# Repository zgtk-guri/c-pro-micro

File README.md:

# c-pro-micro
The atmega32u4 micro-controller board with USB Type-C receptacle, which is compatible with SparkFun Pro Micro

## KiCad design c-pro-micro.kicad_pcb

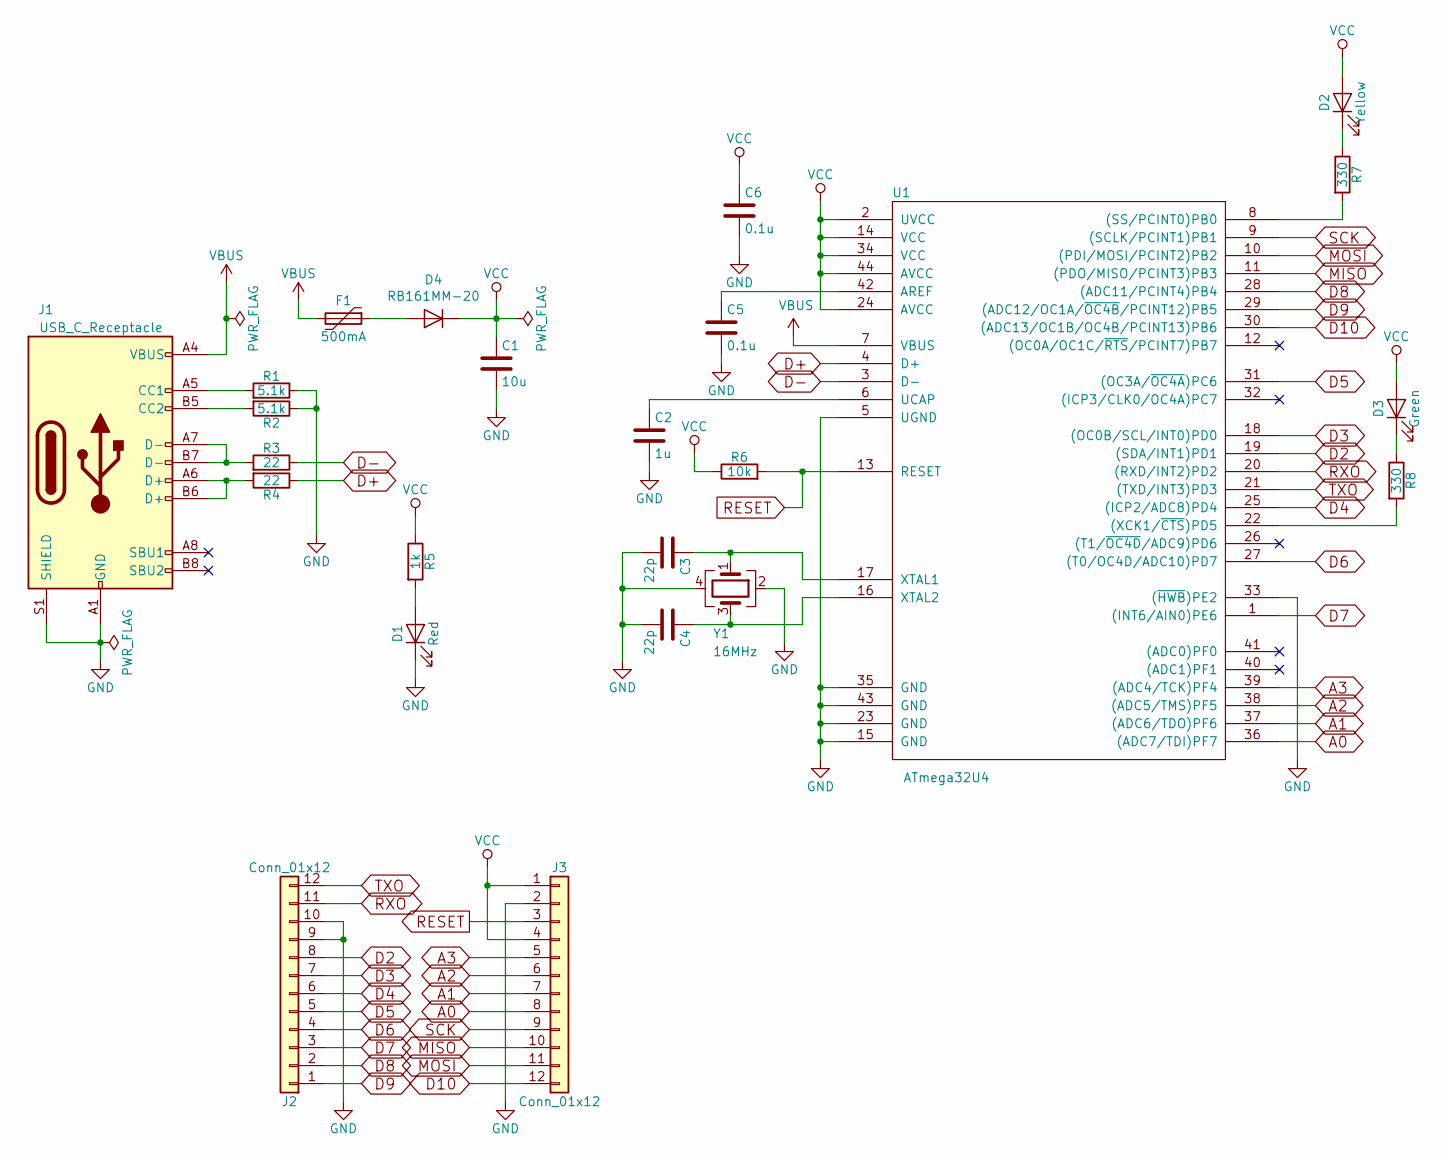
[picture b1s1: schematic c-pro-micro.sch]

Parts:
C1: 10u; C_0603_1608Metric; MPN CL10A106KP8NNNC
C2: 1u; C_0402_1005Metric
C3, C4: 22p; C_0402_1005Metric; MPN 0402CG220J500NT
C5, C6: 0.1u; C_0402_1005Metric; MPN CL05B104KO5NNNC
D1: Red; LED_0603_1608Metric
D2: Yellow; LED_0603_1608Metric
D3: Green; LED_0603_1608Metric
D4: RB161MM-20; D_SOD-123F
F1: 500mA; Fuse_1206_3216Metric
J1: USB_C_Receptacle; CX90M-16P; MPN CX90M-16P; DigikeyPN H126318CT-ND
J2: Conn_01x12; ProMicro_LeftPinhead
J3: Conn_01x12; ProMicro_RightPinhead
R1, R2: 5.1k; R_0402_1005Metric; MPN 0603WAF5101T5E
R3, R4: 22; R_0402_1005Metric; MPN 0402WGF220JTCE
R5: 1k; R_0402_1005Metric; MPN 0402WGF1001TCE
R6: 10k; R_0402_1005Metric; MPN 0402WGF1002TCE
R7, R8: 330; R_0402_1005Metric
U1: ATmega32U4; QFN-44-1EP_7x7mm_Pitch0.5mm_without_bottom; MPN ATMEGA32U4-MUR; DigikeyPN ATMEGA32U4-MURCT-ND
Y1: 16MHz; Crystal_SMD_SeikoEpson_FA238-4Pin_3.2x2.5mm; MPN FA-238 16.0000MB-C3; DigikeyPN SER3686CT-ND

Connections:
A0: J3.8, U1.36 ((ADC7/TDI)PF7)
A1: J3.7, U1.37 ((ADC6/TDO)PF6)
A2: J3.6, U1.38 ((ADC5/TMS)PF5)
A3: J3.5, U1.39 ((ADC4/TCK)PF4)
D2: J2.8, U1.19 ((SDA/INT1)PD1)
D3: J2.7, U1.18 ((OC0B/SCL/INT0)PD0)
D4: J2.6, U1.25 ((ICP2/ADC8)PD4)
D5: J2.5, U1.31 ((OC3A/~OC4A~)PC6)
D6: J2.4, U1.27 ((T0/OC4D/ADC10)PD7)
D7: J2.3, U1.1 ((INT6/AIN0)PE6)
D8: J2.2, U1.28 ((ADC11/PCINT4)PB4)
D9: J2.1, U1.29 ((ADC12/OC1A/~OC4B~/PCINT12)PB5)
D10: J3.12, U1.30 ((ADC13/OC1B/OC4B/PCINT13)PB6)
D+: R4.1, U1.4 (D+)
D-: R3.1, U1.3 (D-)
GND: C1.2, C2.2, C3.2, C4.2, C5.2, C6.2, D1.1 (K), J1.A1 (GND), J1.A12 (GND), J1.B1 (GND), J1.B12 (GND), J1.S1 (SHIELD), J2.9, J2.10, J3.2, R1.1, R2.1, U1.5 (UGND), U1.15 (GND), U1.23 (GND), U1.33 ((~HWB~)PE2), U1.35 (GND), U1.43 (GND), Y1.2, Y1.4
MISO: J3.10, U1.11 ((PDO/MISO/PCINT3)PB3)
MOSI: J3.11, U1.10 ((PDI/MOSI/PCINT2)PB2)
unnamed: C2.1, U1.6 (UCAP)
unnamed: C3.1, U1.17 (XTAL1), Y1.1
unnamed: C4.1, U1.16 (XTAL2), Y1.3
unnamed: C5.1, U1.42 (AREF)
unnamed: D1.2 (A), R5.2
unnamed: D2.1 (K), R7.1
unnamed: D3.1 (K), R8.1
unnamed: D4.2 (A), F1.1
unnamed: J1.A5 (CC1), R1.2
unnamed: J1.A6 (D+), J1.B6 (D+), R4.2
unnamed: J1.A7 (D-), J1.B7 (D-), R3.2
unnamed: J1.B5 (CC2), R2.2
unnamed: R7.2, U1.8 ((SS/PCINT0)PB0)
unnamed: R8.2, U1.22 ((XCK1/~CTS~)PD5)
RESET: J3.3, R6.2, U1.13 (RESET)
RXO: J2.11, U1.20 ((RXD/INT2)PD2)
SCK: J3.9, U1.9 ((SCLK/PCINT1)PB1)
TXO: J2.12, U1.21 ((TXD/INT3)PD3)
VBUS: F1.2, J1.A4 (VBUS), J1.A9 (VBUS), J1.B4 (VBUS), J1.B9 (VBUS), U1.7 (VBUS)
VCC: C1.1, C6.1, D2.2 (A), D3.2 (A), D4.1 (K), J3.1, J3.4, R5.1, R6.1, U1.2 (UVCC), U1.14 (VCC), U1.24 (AVCC), U1.34 (VCC), U1.44 (AVCC)

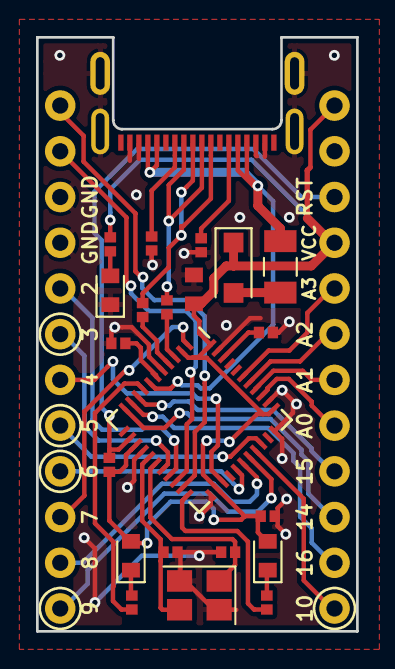
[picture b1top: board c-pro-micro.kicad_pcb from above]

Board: 2 copper layers, 17.8 x 33.0 mm, 24 parts (0 on the bottom side), 38 nets.

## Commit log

2018-04-25 Create KiCad project and add schematic
2018-04-29 add parts informations
2018-04-30 Change components footprint
2018-04-30 Add pcb
2018-05-04 add schematic
2019-01-27 change through hole diameter to 0.9mm
2019-01-27 Rev2
2019-01-27 Create LICENCE
2020-08-15 Rev3
